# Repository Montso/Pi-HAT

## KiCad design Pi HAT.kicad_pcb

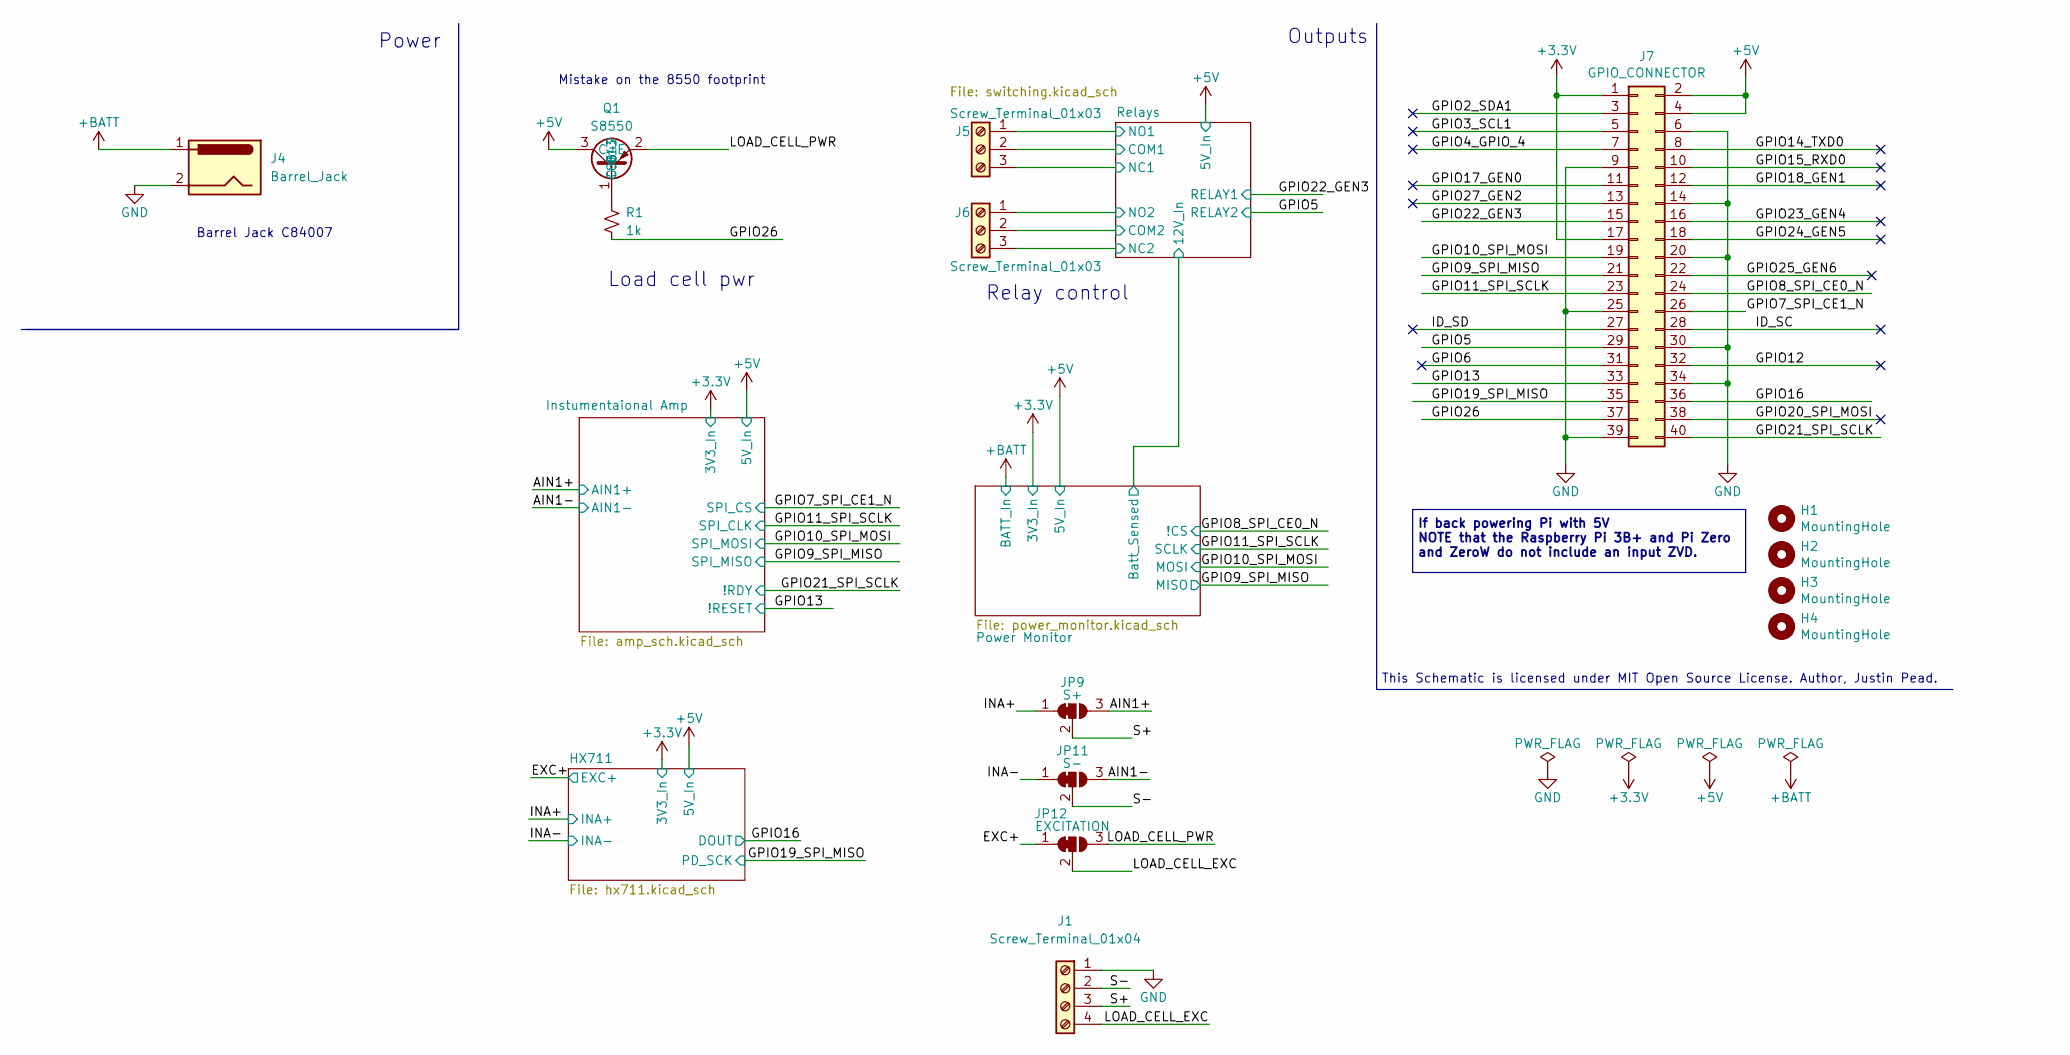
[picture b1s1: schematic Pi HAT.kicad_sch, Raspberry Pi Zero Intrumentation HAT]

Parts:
H1, H2, H3, H4: MountingHole; MountingHole_2.7mm_M2.5_uHAT_RPi
J1: Screw_Terminal_01x04; TerminalBlock_Phoenix_PT-1,5-4-3.5-H_1x04_P3.50mm_Horizontal; LCSC C5144867
J4: Barrel_Jack; Barrel_Jack_2A_C84007; LCSC C84007
J5, J6: Screw_Terminal_01x03; TerminalBlock_Phoenix_PT-1,5-3-3.5-H_1x03_P3.50mm_Horizontal; LCSC C3816291
J7: GPIO_CONNECTOR; PinSocket_2x20_P2.54mm_Vertical_Centered_Anchor
JP9: S+; SolderJumper-3_P1.3mm_Bridged2Bar12_RoundedPad1.0x1.5mm
JP11: S-; SolderJumper-3_P1.3mm_Bridged2Bar12_RoundedPad1.0x1.5mm
JP12: EXCITATION; SolderJumper-3_P1.3mm_Bridged2Bar12_RoundedPad1.0x1.5mm
Q1: S8550; SOT-23; LCSC C8542
R1: 1k; R_0402_1005Metric; LCSC C11702

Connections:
+3.3V: J7.1, J7.17; also elsewhere on the board
+5V: J7.2, J7.4, Q1.3 (C); also elsewhere on the board
+BATT: J4.1; also elsewhere on the board
/AIN1+: JP9.3 (B); also elsewhere on the board
/AIN1-: JP11.3 (B); also elsewhere on the board
/EXC+: JP12.1 (A); also elsewhere on the board
/GPIO2_SDA1: J7.3
/GPIO3_SCL1: J7.5
/GPIO4_GPIO_4: J7.7
/GPIO5: J7.29; also elsewhere on the board
/GPIO6: J7.31
/GPIO7_SPI_CE1_N: J7.26; also elsewhere on the board
/GPIO8_SPI_CE0_N: J7.24; also elsewhere on the board
/GPIO9_SPI_MISO: J7.21; also elsewhere on the board
/GPIO10_SPI_MOSI: J7.19; also elsewhere on the board
/GPIO11_SPI_SCLK: J7.23; also elsewhere on the board
/GPIO12: J7.32
/GPIO13: J7.33; also elsewhere on the board
/GPIO14_TXD0: J7.8
/GPIO15_RXD0: J7.10
/GPIO16: J7.36; also elsewhere on the board
/GPIO17_GEN0: J7.11
/GPIO18_GEN1: J7.12
/GPIO19_SPI_MISO: J7.35; also elsewhere on the board
/GPIO20_SPI_MOSI: J7.38
/GPIO21_SPI_SCLK: J7.40; also elsewhere on the board
/GPIO22_GEN3: J7.15; also elsewhere on the board
/GPIO23_GEN4: J7.16
/GPIO24_GEN5: J7.18
/GPIO25_GEN6: J7.22
/GPIO26: J7.37, R1.2
/GPIO27_GEN2: J7.13
/ID_SC: J7.28
/ID_SD: J7.27
/INA+: JP9.1 (A); also elsewhere on the board
/INA-: JP11.1 (A); also elsewhere on the board
/LOAD_CELL_EXC: J1.4, JP12.2 (C)
/LOAD_CELL_PWR: JP12.3 (B), Q1.2 (E)
/Relays/COM1: J5.2; also elsewhere on the board
/Relays/COM2: J6.2; also elsewhere on the board
/Relays/NC1: J5.3; also elsewhere on the board
/Relays/NC2: J6.3; also elsewhere on the board
/Relays/NO1: J5.1; also elsewhere on the board
/Relays/NO2: J6.1; also elsewhere on the board
/S+: J1.3, JP9.2 (C)
/S-: J1.2, JP11.2 (C)
GND: J1.1, J4.2, J7.6, J7.9, J7.14, J7.20, J7.25, J7.30, J7.34, J7.39; also elsewhere on the board
unnamed: Q1.1 (B), R1.1

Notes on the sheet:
Barrel Jack C84007
This Schematic is licensed under MIT Open Source License. Author, Justin Pead.
Power
Outputs
If back powering Pi with 5V NOTE that the Raspberry Pi 3B+ and Pi Zero and ZeroW do not include an input ZVD.
Load cell pwr
Mistake on the 8550 footprint
Relay control

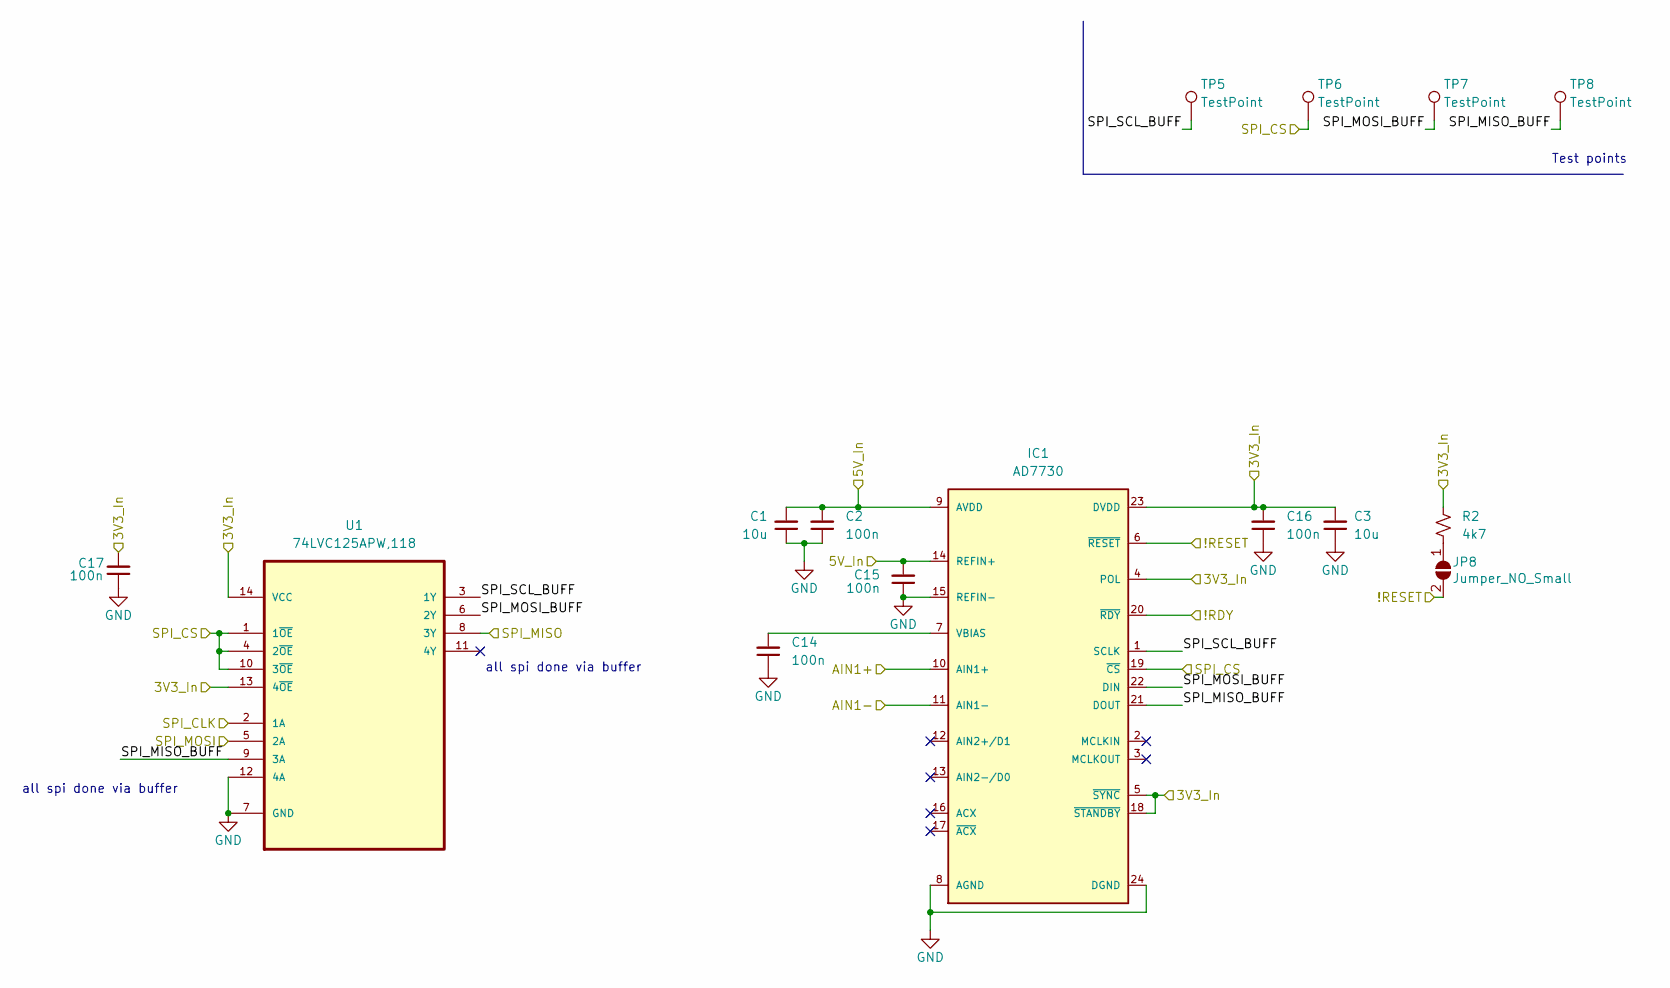
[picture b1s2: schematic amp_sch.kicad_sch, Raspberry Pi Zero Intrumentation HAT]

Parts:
C1, C3: 10u; C_0603_1608Metric; LCSC C96446
C2, C14, C16, C17: 100n; C_0603_1608Metric
C15: 100n; C_0603_1608Metric; LCSC C96446
IC1: AD7730; TSSOP-24_4.4x7.8mm_P0.65mm
JP8: Jumper_NO_Small; SolderJumper-2_P1.3mm_Open_RoundedPad1.0x1.5mm
R2: 4k7; R_0402_1005Metric; LCSC C25900
TP5, TP6, TP7, TP8: TestPoint; TestPoint_Pad_D1.5mm
U1: 74LVC125APW,118; SOP65P640X110-14N; MPN 74LVC125APW,118; LCSC C6059

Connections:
+3.3V: C3.2, C16.2, C17.2, IC1.4 (POL), IC1.5 (~SYNC), IC1.18 (~STANDBY), IC1.23 (DVDD), R2.2, U1.13 (4~OE), U1.14 (VCC); also elsewhere on the board
+5V: C1.2, C2.2, C15.2, IC1.9 (AVDD), IC1.14 (REFIN+); also elsewhere on the board
/AIN1+: IC1.10 (AIN1+); also elsewhere on the board
/AIN1-: IC1.11 (AIN1-); also elsewhere on the board
/GPIO7_SPI_CE1_N: IC1.19 (~CS), TP6.1, U1.1 (1~OE), U1.4 (2~OE), U1.10 (3~OE); also elsewhere on the board
/GPIO9_SPI_MISO: U1.8 (3Y); also elsewhere on the board
/GPIO10_SPI_MOSI: U1.5 (2A); also elsewhere on the board
/GPIO11_SPI_SCLK: U1.2 (1A); also elsewhere on the board
/GPIO13: IC1.6 (~RESET), JP8.2 (B); also elsewhere on the board
/GPIO21_SPI_SCLK: IC1.20 (~RDY); also elsewhere on the board
/Instumentaional Amp/SPI_MISO_BUFF: IC1.21 (DOUT), TP8.1, U1.9 (3A)
/Instumentaional Amp/SPI_MOSI_BUFF: IC1.22 (DIN), TP7.1, U1.6 (2Y)
/Instumentaional Amp/SPI_SCL_BUFF: IC1.1 (SCLK), TP5.1, U1.3 (1Y)
GND: C1.1, C2.1, C3.1, C14.1, C15.1, C16.1, C17.1, IC1.8 (AGND), IC1.15 (REFIN-), IC1.24 (DGND), U1.7 (GND), U1.12 (4A); also elsewhere on the board
unnamed: C14.2, IC1.7 (VBIAS)
unnamed: JP8.1 (A), R2.1

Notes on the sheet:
all spi done via buffer
Test points

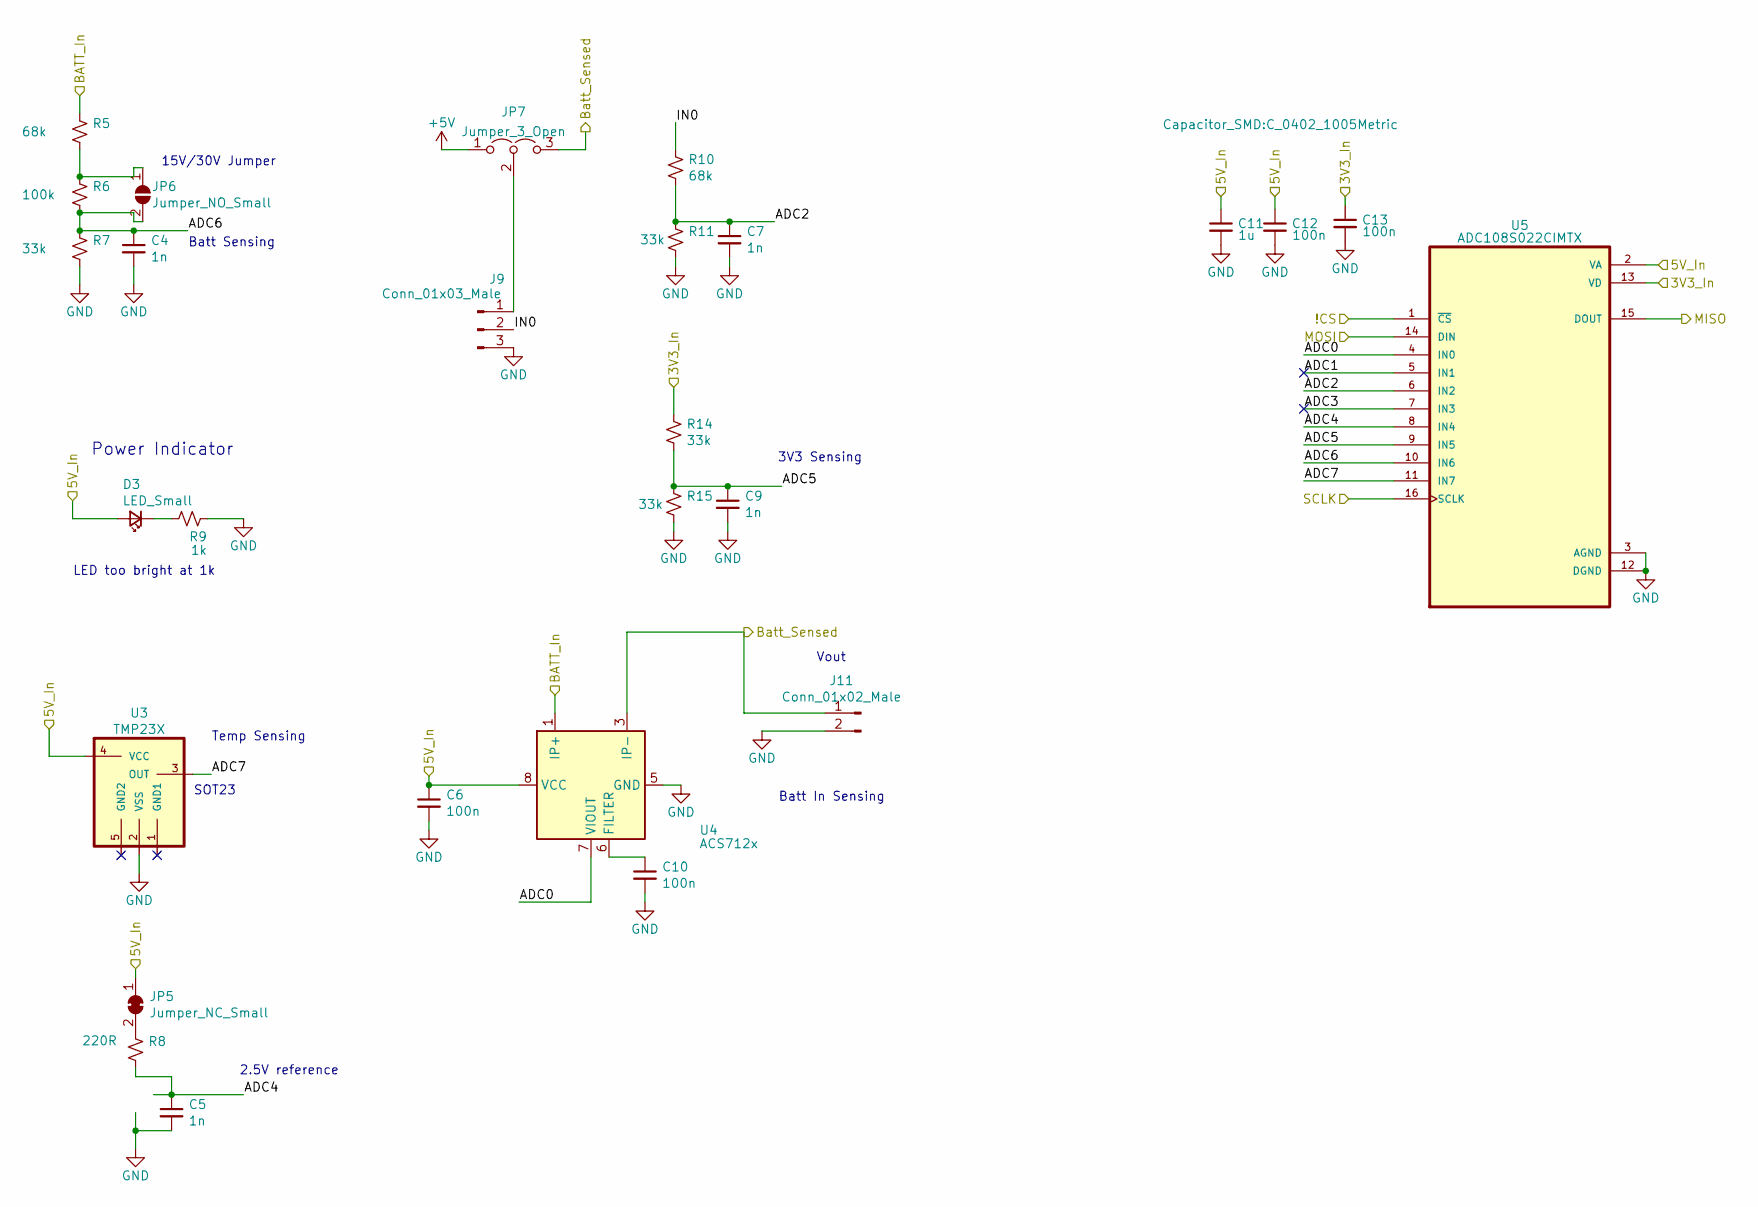
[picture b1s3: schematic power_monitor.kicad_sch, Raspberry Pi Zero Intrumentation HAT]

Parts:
C4, C5, C7, C9: 1n; C_0402_1005Metric; LCSC C1523
C6, C10, C12, C13: 100n; C_0402_1005Metric; LCSC C307331
C11: 1u; C_0402_1005Metric; LCSC C52923
D3: LED_Small; D_0603_1608Metric; LCSC C2286
J9: Conn_01x03_Male; PinHeader_1x03_P2.54mm_Vertical
J11: Conn_01x02_Male; PinHeader_1x02_P2.54mm_Vertical
JP5: Jumper_NC_Small; SolderJumper-2_P1.3mm_Bridged_RoundedPad1.0x1.5mm
JP6: Jumper_NO_Small; SolderJumper-2_P1.3mm_Open_RoundedPad1.0x1.5mm
JP7: Jumper_3_Open; SolderJumper-3_P2.0mm_Open_TrianglePad1.0x1.5mm
R5, R10: 68k; R_0402_1005Metric; LCSC C36871
R6: 100k; R_0402_1005Metric; LCSC C25741
R7, R11, R14, R15: 33k; R_0402_1005Metric; LCSC C25779
R8: 220R; R_0402_1005Metric; LCSC C25091
R9: 1k; R_0402_1005Metric; LCSC C11702
U3: TMP23X; SOT65P210X110-5N; LCSC C2861437
U4: ACS712x; SOIC-8_3.9x4.9mm_P1.27mm; LCSC C44471
U5: ADC108S022CIMTX; SOP65P640X120-16N; MPN ADC108S022CIMTX

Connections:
+3.3V: C13.1, R14.1, U5.13 (VD); also elsewhere on the board
+5V: C6.1, C11.1, C12.1, D3.2 (A), JP5.1 (A), JP7.1 (A), U3.4 (VCC), U4.8 (VCC), U5.2 (VA); also elsewhere on the board
+BATT: R5.1, U4.1 (IP+), U4.2 (IP+); also elsewhere on the board
/GPIO8_SPI_CE0_N: U5.1 (~CS); also elsewhere on the board
/GPIO9_SPI_MISO: U5.15 (DOUT); also elsewhere on the board
/GPIO10_SPI_MOSI: U5.14 (DIN); also elsewhere on the board
/GPIO11_SPI_SCLK: U5.16 (SCLK); also elsewhere on the board
/Power Monitor/ADC0: U4.7 (VIOUT), U5.4 (IN0)
/Power Monitor/ADC1: U5.5 (IN1)
/Power Monitor/ADC2: C7.1, R10.2, R11.1, U5.6 (IN2)
/Power Monitor/ADC3: U5.7 (IN3)
/Power Monitor/ADC4: C5.1, R8.2, U5.8 (IN4)
/Power Monitor/ADC5: C9.1, R14.2, R15.1, U5.9 (IN5)
/Power Monitor/ADC6: C4.1, JP6.2 (B), R6.2, R7.1, U5.10 (IN6)
/Power Monitor/ADC7: U3.3 (OUT), U5.11 (IN7)
/Power Monitor/Batt_Sensed: J11.1, JP7.3 (B), U4.3 (IP-), U4.4 (IP-); also elsewhere on the board
/Power Monitor/IN0: J9.2, R10.1
GND: C4.2, C5.2, C6.2, C7.2, C9.2, C10.2, C11.2, C12.2, C13.2, J9.3, J11.2, R7.2, R9.2, R11.2, R15.2, U3.2 (VSS), U4.5 (GND), U5.3 (AGND), U5.12 (DGND); also elsewhere on the board
unnamed: D3.1 (K), R9.1
unnamed: J9.1, JP7.2 (C)
unnamed: JP5.2 (B), R8.1
unnamed: JP6.1 (A), R5.2, R6.1
unnamed: C10.1, U4.6 (FILTER)

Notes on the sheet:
SOT23
Power Indicator
3V3 Sensing
Batt In Sensing
2.5V reference
LED too bright at 1k
Temp Sensing
15V/30V Jumper
Vout
Batt Sensing

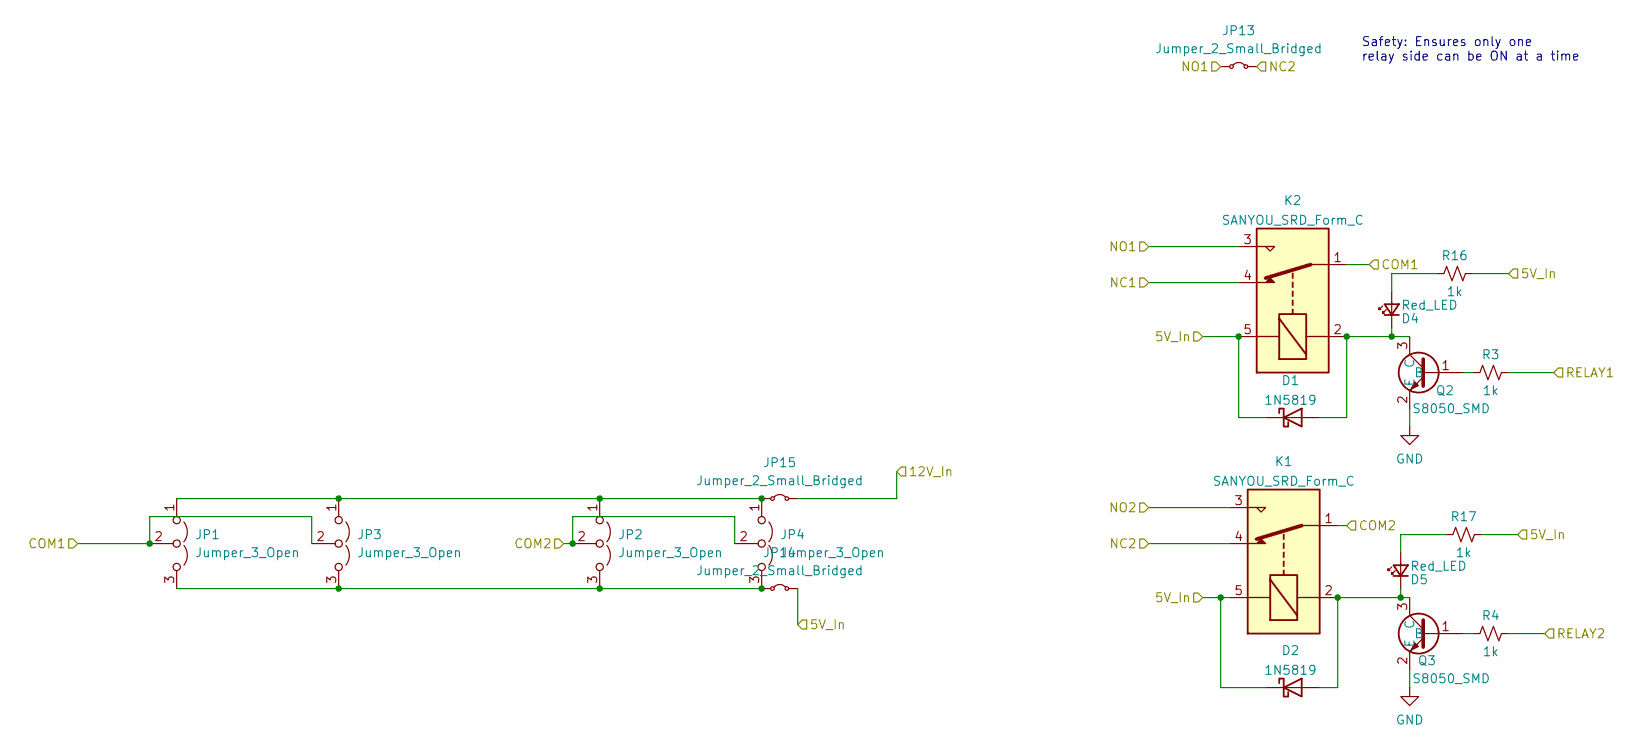
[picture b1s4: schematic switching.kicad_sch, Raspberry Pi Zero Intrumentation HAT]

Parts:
D1, D2: 1N5819; D_SOD-123; LCSC C8598
D4, D5: Red_LED; D_0603_1608Metric; LCSC C2286
JP1, JP2, JP3, JP4: Jumper_3_Open; SolderJumper-3_P2.0mm_Open_TrianglePad1.0x1.5mm
JP13: Jumper_2_Small_Bridged; SolderJumper-2_P1.3mm_Bridged_RoundedPad1.0x1.5mm
JP14, JP15: Jumper_2_Small_Bridged; Jumper_Open_wide
K1, K2: SANYOU_SRD_Form_C; Relay_SPDT_SANYOU_SRD_Series_Form_C; LCSC C35449
Q2, Q3: S8050_SMD; SOT-23; LCSC C2150
R3, R4, R16, R17: 1k; R_0402_1005Metric; LCSC C11702

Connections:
+5V: D1.1 (K), D2.1 (K), JP14.2 (B), K1.5, K2.5, R16.2, R17.2; also elsewhere on the board
/GPIO5: R4.2; also elsewhere on the board
/GPIO22_GEN3: R3.2; also elsewhere on the board
/Power Monitor/Batt_Sensed: JP15.2 (B); also elsewhere on the board
/Relays/COM1: JP1.2 (C), JP3.2 (C), K2.1; also elsewhere on the board
/Relays/COM2: JP2.2 (C), JP4.2 (C), K1.1; also elsewhere on the board
/Relays/NC1: K2.4; also elsewhere on the board
/Relays/NC2: JP13.2 (B), K1.4; also elsewhere on the board
/Relays/NO1: JP13.1 (A), K2.3; also elsewhere on the board
/Relays/NO2: K1.3; also elsewhere on the board
GND: Q2.2 (E), Q3.2 (E); also elsewhere on the board
unnamed: D1.2 (A), D4.1 (K), K2.2, Q2.3 (C)
unnamed: D2.2 (A), D5.1 (K), K1.2, Q3.3 (C)
unnamed: D4.2 (A), R16.1
unnamed: D5.2 (A), R17.1
unnamed: JP1.1 (A), JP2.1 (A), JP3.1 (A), JP4.1 (A), JP15.1 (A)
unnamed: JP1.3 (B), JP2.3 (B), JP3.3 (B), JP4.3 (B), JP14.1 (A)
unnamed: Q2.1 (B), R3.1
unnamed: Q3.1 (B), R4.1

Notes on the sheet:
Safety: Ensures only one relay side can be ON at a time

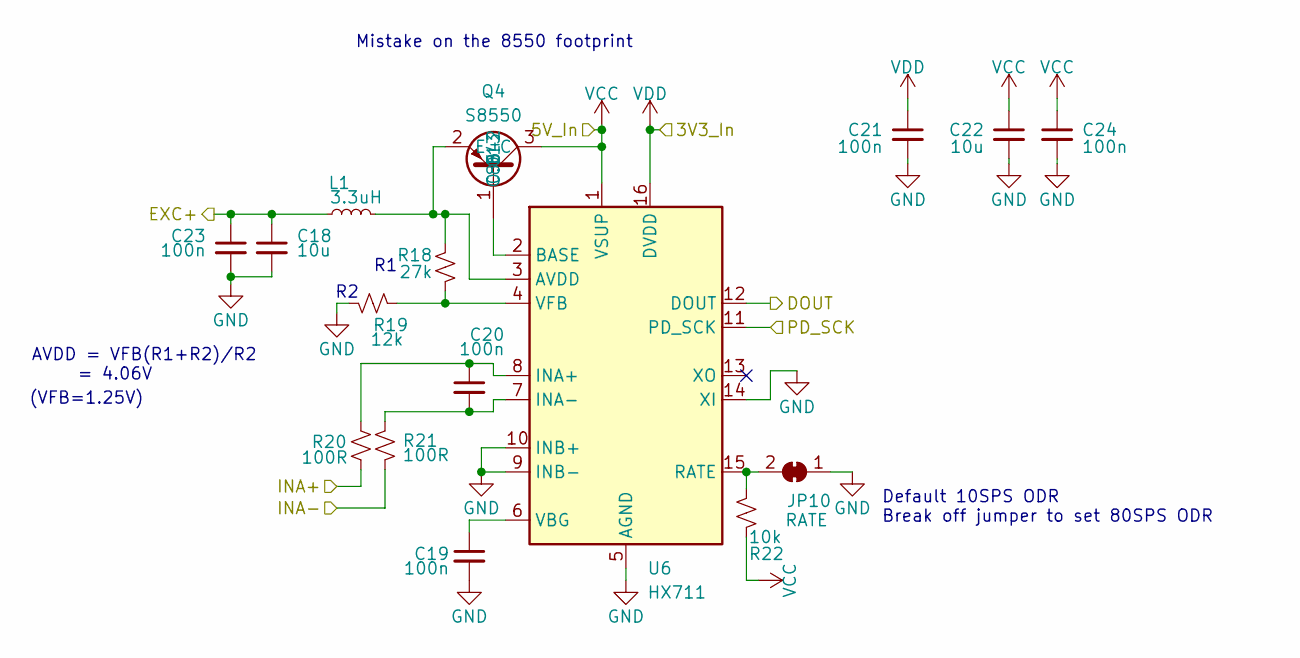
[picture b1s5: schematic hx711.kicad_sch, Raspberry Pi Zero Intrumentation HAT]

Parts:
C18, C22: 10u; C_0603_1608Metric
C19, C20, C21, C24: 100n; C_0402_1005Metric
C23: 100n; C_0603_1608Metric
JP10: RATE; SolderJumper-2_P1.3mm_Bridged_RoundedPad1.0x1.5mm
L1: 3.3uH; L_0603_1608Metric
Q4: S8550; SOT-23; LCSC C8542
R18: 27k; R_0402_1005Metric
R19: 12k; R_0402_1005Metric
R20, R21: 100R; R_0402_1005Metric
R22: 10k; R_0402_1005Metric
U6: HX711; SOP-16_3.9x9.9mm_P1.27mm

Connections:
+3.3V: C21.1, U6.16 (DVDD); also elsewhere on the board
+5V: C22.1, C24.1, Q4.3 (C), R22.2, U6.1 (VSUP); also elsewhere on the board
/EXC+: C18.1, C23.1, L1.1; also elsewhere on the board
/GPIO16: U6.12 (DOUT); also elsewhere on the board
/GPIO19_SPI_MISO: U6.11 (PD_SCK); also elsewhere on the board
/INA+: R20.1; also elsewhere on the board
/INA-: R21.1; also elsewhere on the board
GND: C18.2, C19.2, C21.2, C22.2, C23.2, C24.2, JP10.1 (A), R19.1, U6.5 (AGND), U6.9 (INB-), U6.10 (INB+), U6.14 (XI); also elsewhere on the board
unnamed: JP10.2 (B), R22.1, U6.15 (RATE)
unnamed: Q4.1 (B), U6.2 (BASE)
unnamed: L1.2, Q4.2 (E), R18.1, U6.3 (AVDD)
unnamed: C20.1, R20.2, U6.8 (INA+)
unnamed: C20.2, R21.2, U6.7 (INA-)
unnamed: C19.1, U6.6 (VBG)
unnamed: R18.2, R19.2, U6.4 (VFB)

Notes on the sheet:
Default 10SPS ODR Break off jumper to set 80SPS ODR
AVDD = VFB(R1+R2)/R2 = 4.06V
(VFB=1.25V)
Mistake on the 8550 footprint

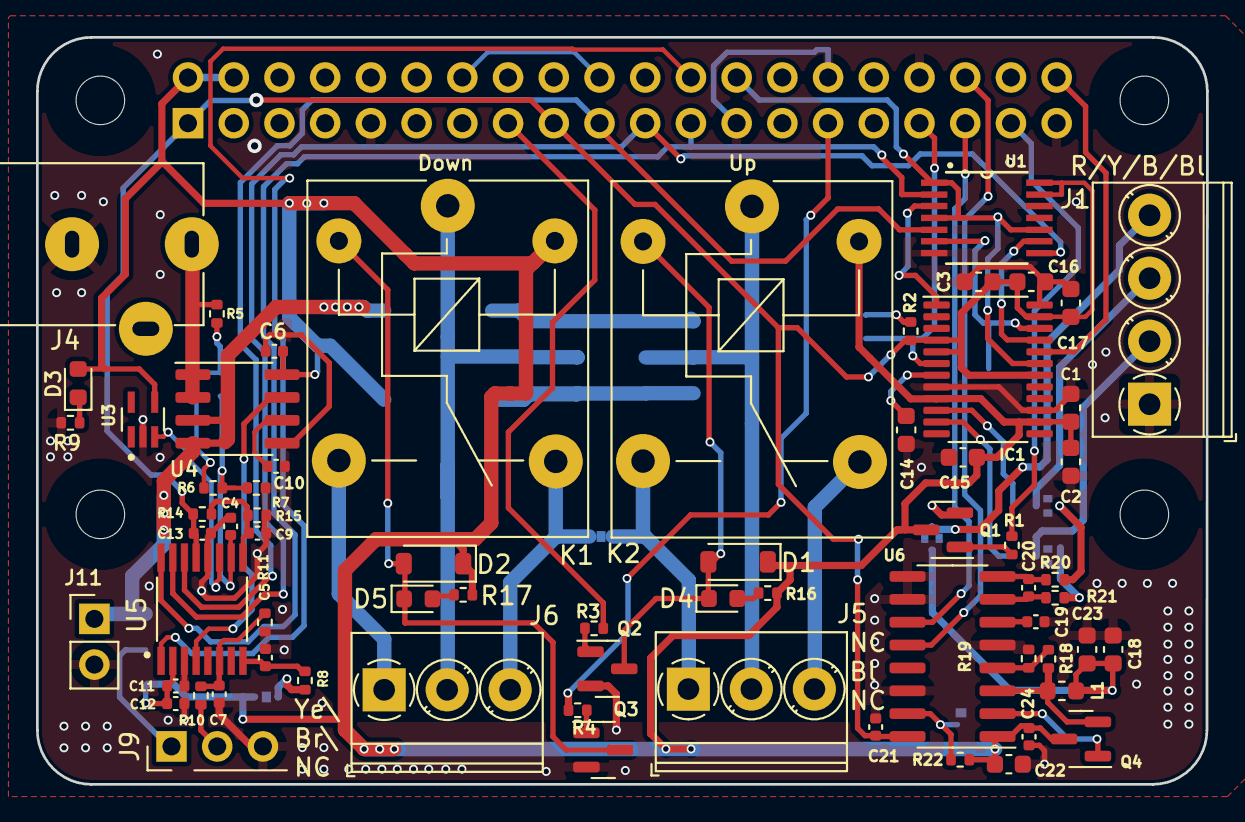
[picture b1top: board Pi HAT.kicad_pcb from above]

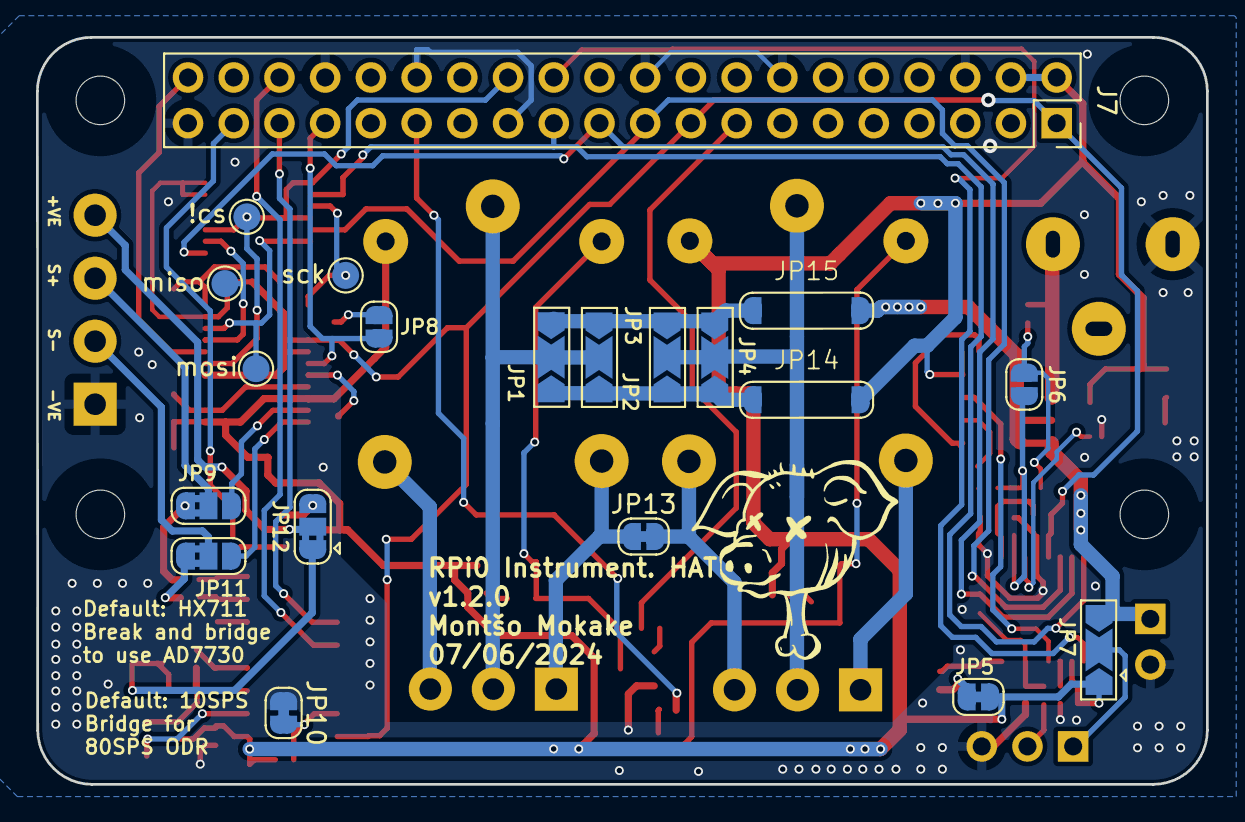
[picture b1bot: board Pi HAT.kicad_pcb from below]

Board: 2 copper layers, 65.0 x 41.5 mm, 91 parts (20 on the bottom side), 65 nets.

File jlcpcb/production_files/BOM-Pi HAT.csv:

Comment,Designator,Footprint,LCSC
1k,"R1,R3,R4,R9",R_0402_1005Metric,C11702
100n,"C14,C16,C17,C2,C23",C_0603_1608Metric,C14663
1n,"C4,C5,C7,C9",C_0402_1005Metric,C1523
10u,"C18,C22",C_0603_1608Metric,C19702
S8050_SMD,"Q2,Q3",SOT-23,C2150
LED_Small,"D3,D4,D5",D_0603_1608Metric,C2286
100R,"R20,R21",R_0402_1005Metric,C25076
120R,"R16,R17",R_0402_1005Metric,C25079
220R,R8,R_0402_1005Metric,C25091
100k,R6,R_0402_1005Metric,C25741
10k,R22,R_0402_1005Metric,C25744
12k,R19,R_0402_1005Metric,C25752
27k,R18,R_0402_1005Metric,C25771
33k,"R11,R14,R15,R7",R_0402_1005Metric,C25779
4k7,R2,R_0402_1005Metric,C25900
3.3uH,L1,L_0603_1608Metric,C275346
TMP23X,U3,SOT65P210X110-5N,C2861437
100n,"C10,C12,C13,C19,C20,C21,C24,C6",C_0402_1005Metric,C307331
CJ431,U2,SOT-23,C3113
SANYOU_SRD_Form_C,"K1,K2",Relay_SPDT_SANYOU_SRD_Series_Form_C,C35449
68k,"R10,R5",R_0402_1005Metric,C36871
Screw_Terminal_01x03,"J5,J6","TerminalBlock_Phoenix_PT-1,5-3-3.5-H_1x03_P3.50mm_Horizontal",C3816291
HX711,U6,SOP-16_3.9x9.9mm_P1.27mm,C43656
ACS712xLCTR-20A,U4,SOIC-8_3.9x4.9mm_P1.27mm,C44471
Screw_Terminal_01x04,J1,"TerminalBlock_Phoenix_PT-1,5-4-3.5-H_1x04_P3.50mm_Horizontal",C5144867
1u,C11,C_0402_1005Metric,C52923
"74LVC125APW,118",U1,SOP65P640X110-14N,C6059
Barrel_Jack,J4,Barrel_Jack_2A_C84007,C84007
S8550,"Q1,Q4",SOT-23,C8542
1N5819,"D1,D2",D_SOD-123,C8598
10u,"C1,C15,C3",C_0603_1608Metric,C96446

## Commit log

2022-10-29 Footprint assignment
    Footprints yet to be assigned:
    -U1: 74LVC125APW
2022-11-01 Buffer footprint added
    -fault in footprint for pi headers and load cell headers
2022-11-03 FIxed J1-Headers conflict
    Added a layout
2022-11-11 Component placement
2022-11-12 Reassigned pins to match placement
2022-11-17 Flipping components to the front side
2022-11-20 placement refinement and indicator LEDs for relays
    -Crude wiring
    -Fixed values
    -Indicator LEDs for relays
    -Added test points
2022-11-24 Wiring and 12V battery_sensed added
2022-11-24 Updated with changes from meeting
2022-12-01 Updated wiring. Test points only added for AD7730.
2022-12-01 Updated wiring.
2022-12-07 Updated via sizes on wiring.
2022-12-08 Used Phoenix connectors. Wired ADC0 track.
2022-12-08 Fixed CE pins. Added GND copper pour on F.Cu.
2022-12-18 Review and fixes on schematic and pcb.
    -Updated Relay LED values.
    -Fixed !RDY and R1 pin conflict on GPIO26.
2023-01-16 Improvements made to the info in the schematic excel sheet and made the files necessary for production
2023-11-22 Changes to the AD7730 based on Montso's working Arduino system
2023-12-05 Changes made to the AD7730 circuit. HX711 circuit added and AD7730 sidestepped.
2023-12-06 Created a folder of additional component libraries
2023-12-06 Deleted individual library directories
2023-12-06 Added footprints for HX711 circuit on PCB and modified pin assignment
2023-12-07 Fixed clearance violations and via sizing violations on pcb. Omitted 'mask aperture bridges' errors for jumpers.
2023-12-07 Made more pcb connections and edited footprints' silkscreens
2023-12-08 Added ground pour and fixed connections
2023-12-08 Updated +3V3 tracks on pcb and buffer schematic
    -Added decoupling cap for buffer
    -Tied unused buffer input 4 to gnd
    -Did all +3V3 connections
    -Fixed +5V tracks
    -gnd stitching
2023-12-08 Updated power circuit. Fixed U1 footprint.
    -Dropped ADC1 and ADC3 connections
    -Dropped IN1 branch
2023-12-08 Silkscreen labelling
2023-12-08 Connected power to relay COMs
2023-12-09 Fixed HX711 decoupling cap. Changed EXC+.
    - Changed EXC+ to 4.06V
    - Consistent values for schematic components
    - Added B.silkscreen art
2023-12-09 Fixed JP10 jumper footprint
2023-12-09 Touch ups following final review.
2023-12-09 Added jlcpcb files. Updated additional libraries
2023-12-12 Fixed jlcpcb folder
2023-12-12 Added jlcpcb files. Removed .csv in ignore.
2023-12-12 Updated .gitignore to include BOM. Recovered GERBERS
2023-12-12 Recovered GERBER-Pi HAT.zip
2023-12-12 Updated BOM. Add parts for pin headers.
2023-12-14 Redone BOM. Uploaded jlcpcb files.
2023-12-14 Changed to 5A variant for current sensor.
2023-12-14 Added silkscreen for U1 footprint.
2023-12-18 Added adc108 datasheet.
2023-12-18 Added CJ431 and TMP235 datasheets.
2024-01-10 Minor tweaks on the board, board pullback, and 8550 error spotted
2024-01-12 Changed some of the wiring on the Jumpers, and changed the footprint for the 8550
2024-01-15 Added rev number for last changes (ad0cc53)
2024-01-19 Update BJT symbols and ver number
2024-01-19 Fixed BJT footprints and adc bridges
    -1.1.x Fixed the BJT pinouts
    -1.1.1 Fixed connections for adc jumpers
    -1.1.2 Add keep-out zone near relay jumpers
2024-01-19 Added gnd stitching vias. Fixed 5v track
2024-06-07 Connected NC2 to COM1
2024-06-07 Connected NO2 to COM1. Annonated relays.
2024-06-24 Ammended it to have the jumper connection
2024-07-01 Modified the PCB to have a greater spacing on anything Relay 2ndary side related
